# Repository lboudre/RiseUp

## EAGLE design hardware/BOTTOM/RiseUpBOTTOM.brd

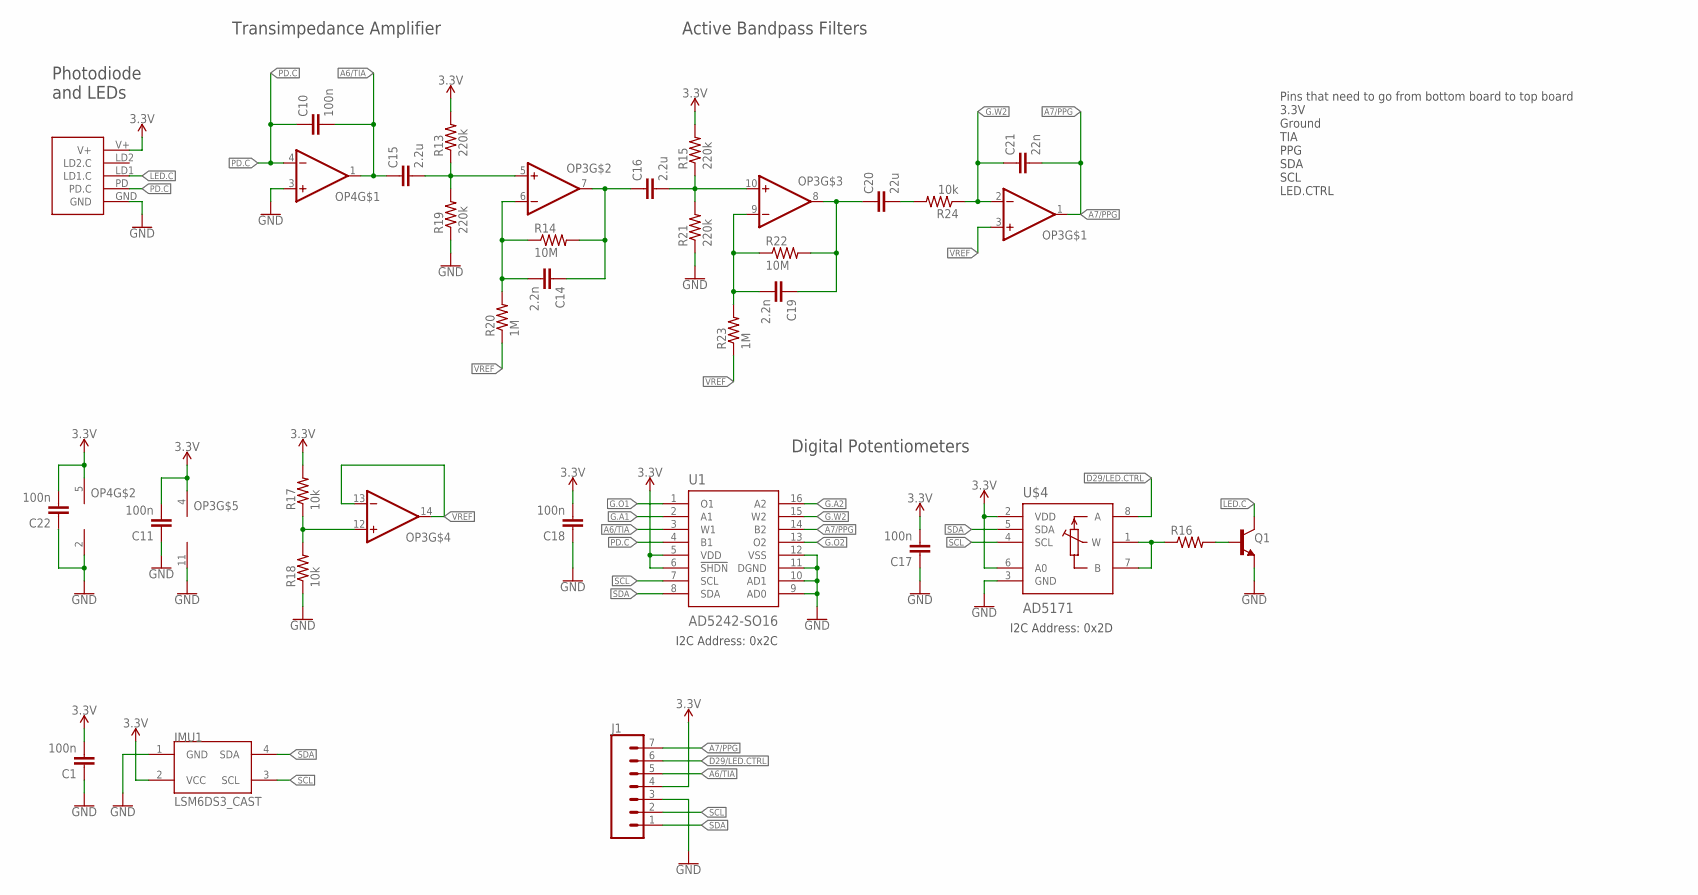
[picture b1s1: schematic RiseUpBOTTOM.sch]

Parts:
C1, C10, C11, C17, C18, C22: 100n; C0603
C14, C19: 2.2n; C0603
C15, C16: 2.2u; C0603
C20: 22u; C0603
C21: 22n; C0603
IMU1: LSM6DS3_CAST
J1: CONN_07; 1X07
OP3: OP-QUAD-SO14; SO14
OP4: OP-SINGLEOT; SOT23-5
Q1: NPN-GENERIC; SOT23-3
R13, R15, R19, R21: 220k; R0603
R14, R22: 10M; R0603
R16: RESISTOR0603; R0603
R17, R18: 10k; R0402
R20, R23: 1M; R0603
R24: 10k; R0603
U1: AD5242-SO16; SO16
U$3: PPG.MODULE.2
U$4: AD5171; SOT-23-8

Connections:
3.3V: C1.2, C11.2, C17.2, C18.2, C22.2, IMU1.2 (VCC), J1.4, OP3.4 (V+), OP4.5 (V+), R13.2, R15.2, R17.2, U1.5 (VDD), U1.6 (!SHDN), U$3.V+, U$4.2 (VDD), U$4.6 (A0)
A6/TIA: C10.2, C15.1, J1.5, OP4.1 (OUT), U1.3 (W1)
A7/PPG: C21.2, J1.7, OP3.1 (OUT), U1.14 (B2)
D29/LED.CTRL: J1.6, U$4.8 (A)
G.A1: U1.2 (A1)
G.A2: U1.16 (A2)
G.O1: U1.1 (O1)
G.O2: U1.13 (O2)
G.W2: C21.1, OP3.2 (-IN), R24.1, U1.15 (W2)
GND: C1.1, C11.1, C17.1, C18.1, C22.1, IMU1.1 (GND), J1.3, OP3.11 (V-), OP4.2 (V-), OP4.3 (+IN), Q1.2 (E), R18.1, R19.1, R21.1, U1.9 (AD0), U1.10 (AD1), U1.11 (DGND), U1.12 (VSS), U$3.GND, U$4.3 (GND)
LED.C: Q1.3 (C), U$3.LD1 (LD1.C)
unnamed: Q1.1 (B), R16.2
unnamed: R16.1, U$4.1 (W), U$4.7 (B)
unnamed: OP3.12 (+IN), R17.1, R18.2
unnamed: C15.2, OP3.5 (+IN), R13.1, R19.2
unnamed: C14.2, OP3.6 (-IN), R14.1, R20.2
unnamed: C14.1, C16.1, OP3.7 (OUT), R14.2
unnamed: C16.2, OP3.10 (+IN), R15.1, R21.2
unnamed: C19.2, OP3.9 (-IN), R22.1, R23.2
unnamed: C19.1, C20.1, OP3.8 (OUT), R22.2
unnamed: C20.2, R24.2
PD.C: C10.1, OP4.4 (-IN), U1.4 (B1), U$3.PD (PD.C)
SCL: IMU1.3 (SCL), J1.2, U1.7 (SCL), U$4.4 (SCL)
SDA: IMU1.4 (SDA), J1.1, U1.8 (SDA), U$4.5 (SDA)
VREF: OP3.3 (+IN), OP3.13 (-IN), OP3.14 (OUT), R20.1, R23.1

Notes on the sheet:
Photodiode and LEDs
Active Bandpass Filters
Digital Potentiometers
Transimpedance Amplifier
I2C Address: 0x2C
I2C Address: 0x2D
Pins that need to go from bottom board to top board 3.3V Ground TIA PPG SDA SCL LED.CTRL

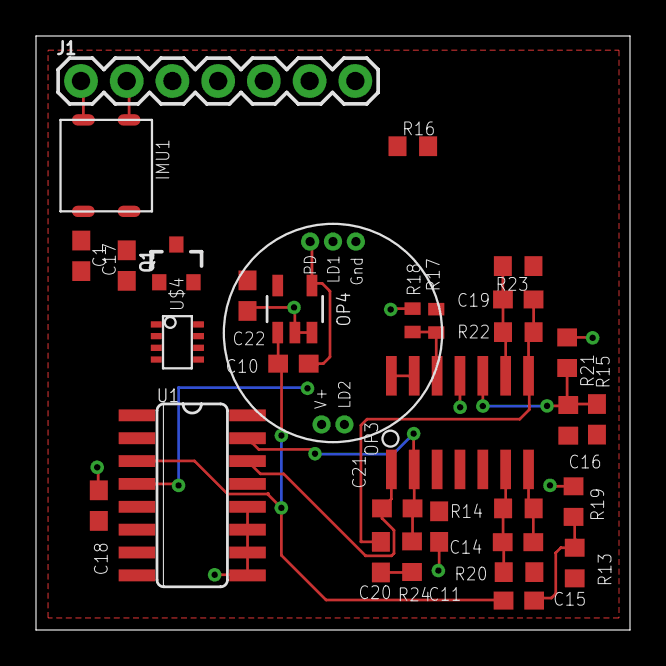
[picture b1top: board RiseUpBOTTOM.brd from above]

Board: 2 copper layers, 33.0 x 33.0 mm, 32 parts (0 on the bottom side), 21 nets.

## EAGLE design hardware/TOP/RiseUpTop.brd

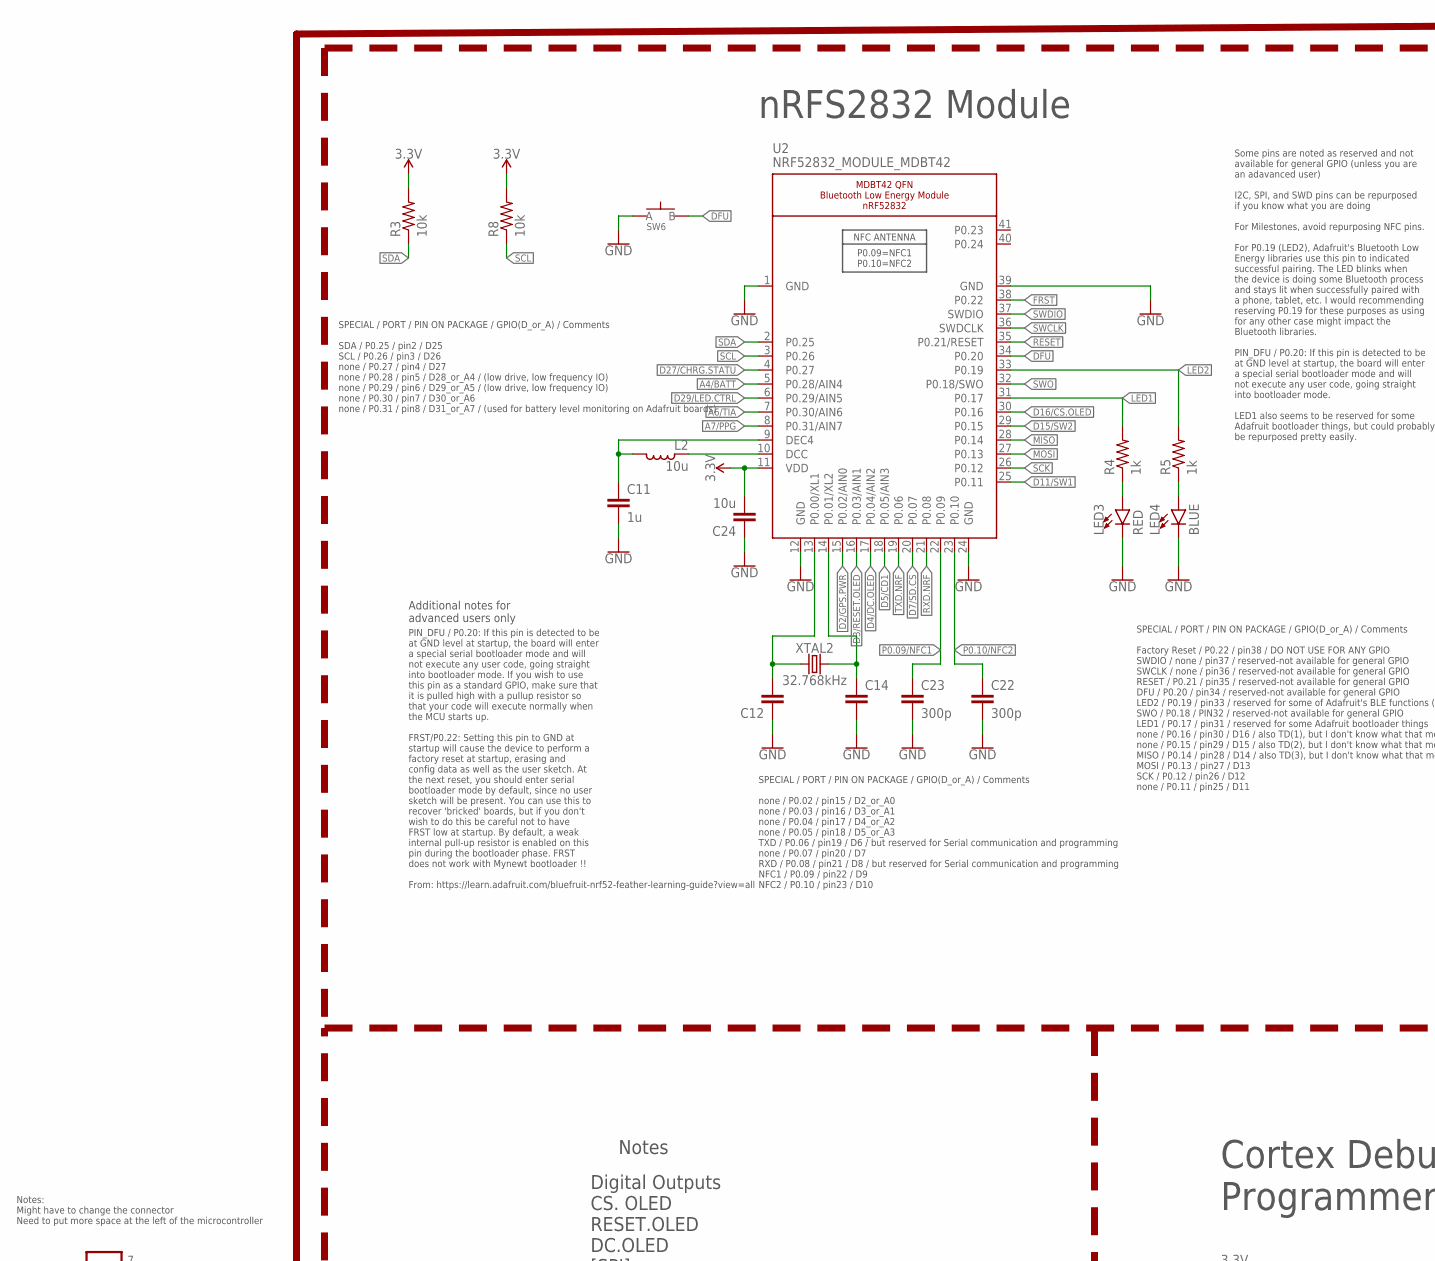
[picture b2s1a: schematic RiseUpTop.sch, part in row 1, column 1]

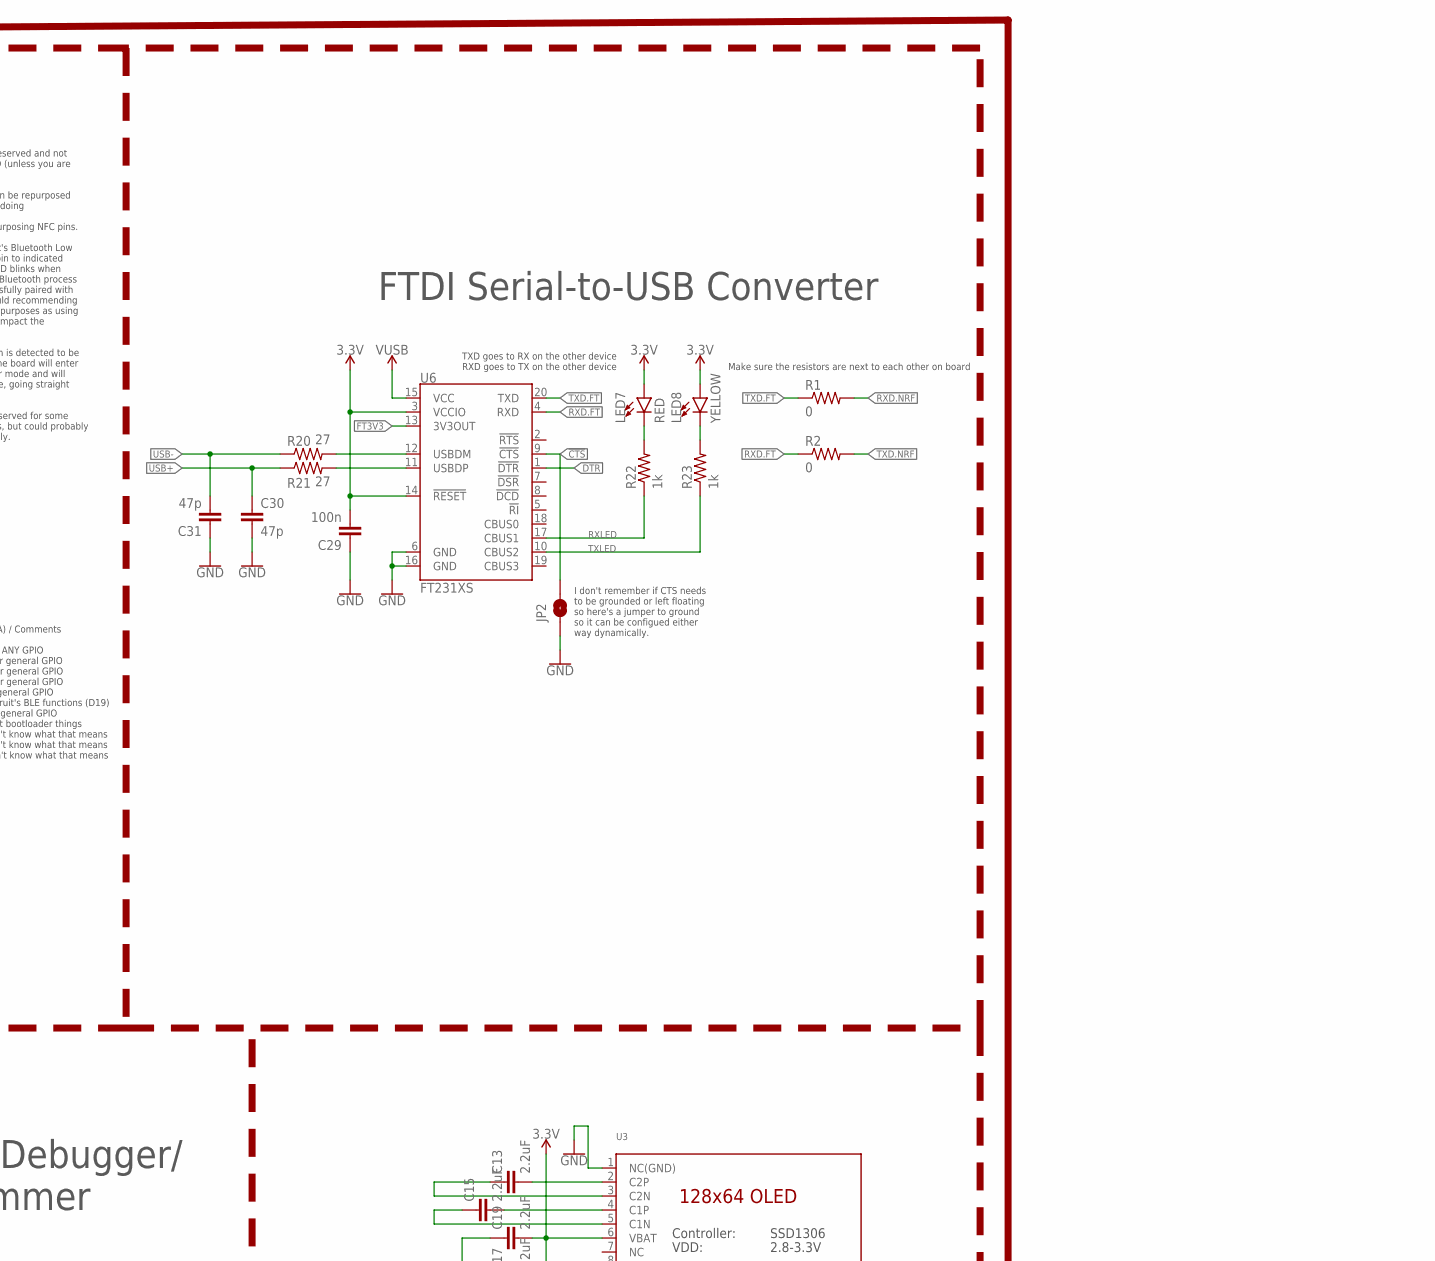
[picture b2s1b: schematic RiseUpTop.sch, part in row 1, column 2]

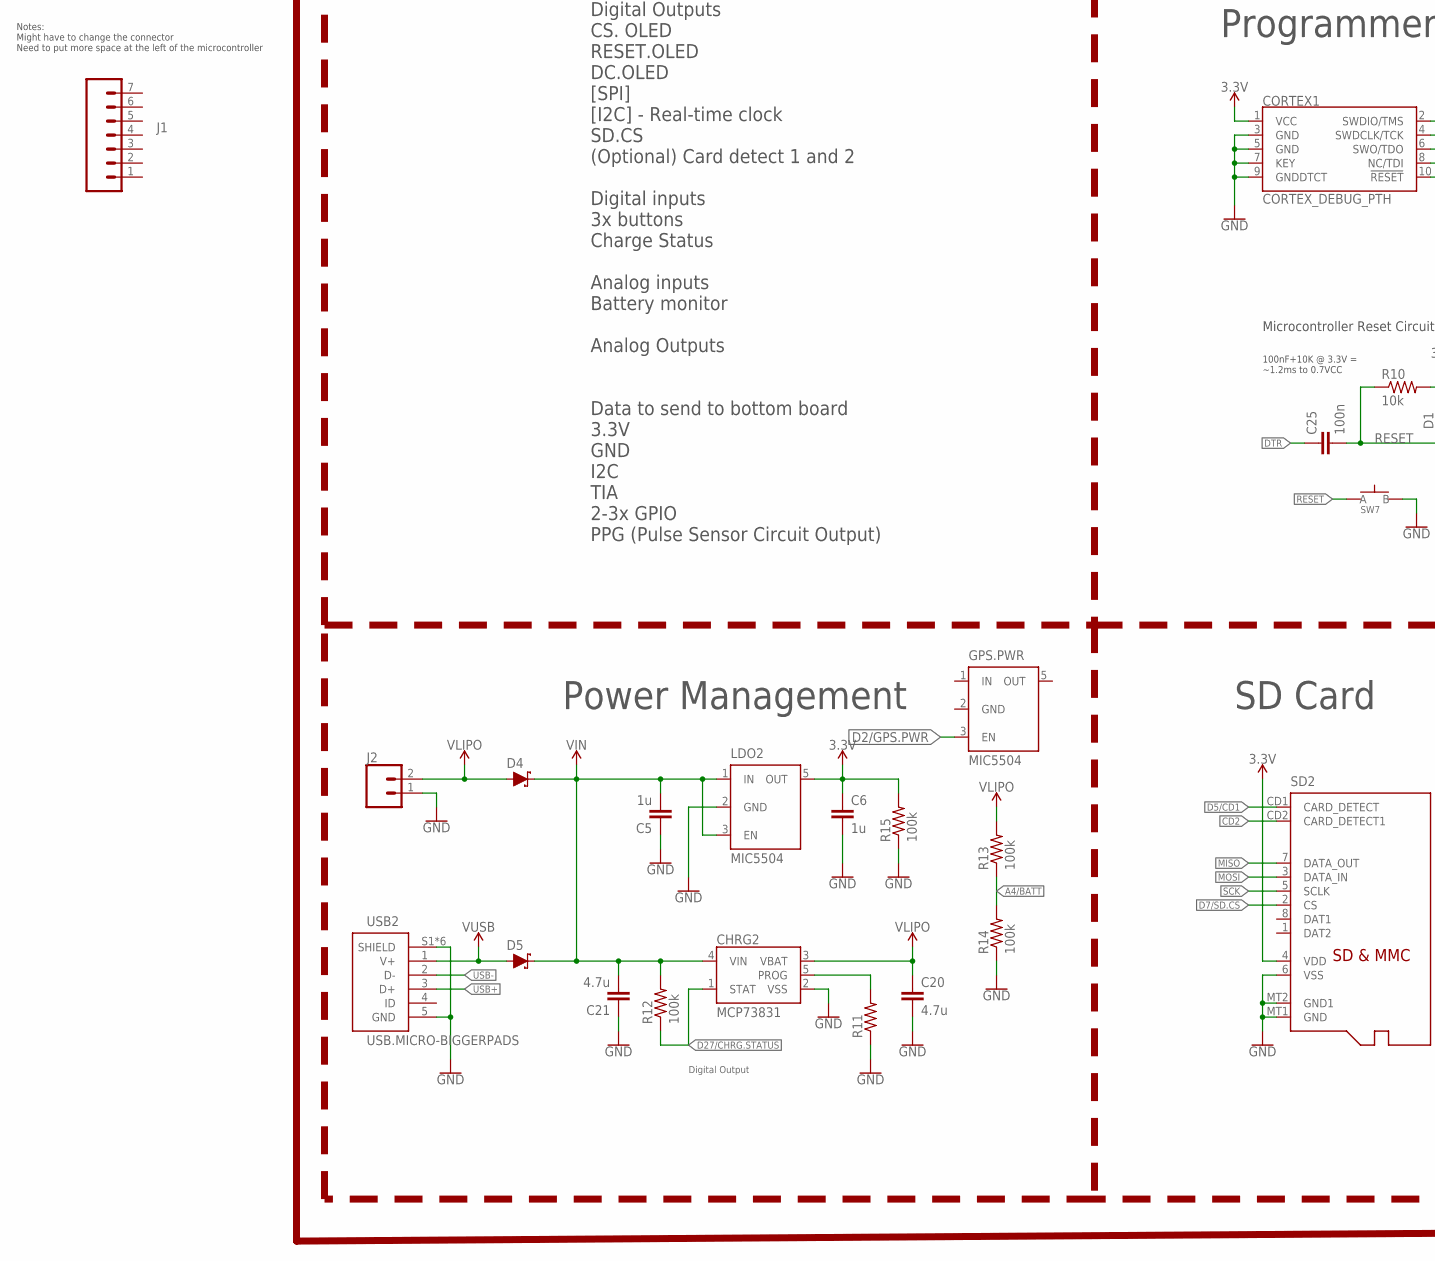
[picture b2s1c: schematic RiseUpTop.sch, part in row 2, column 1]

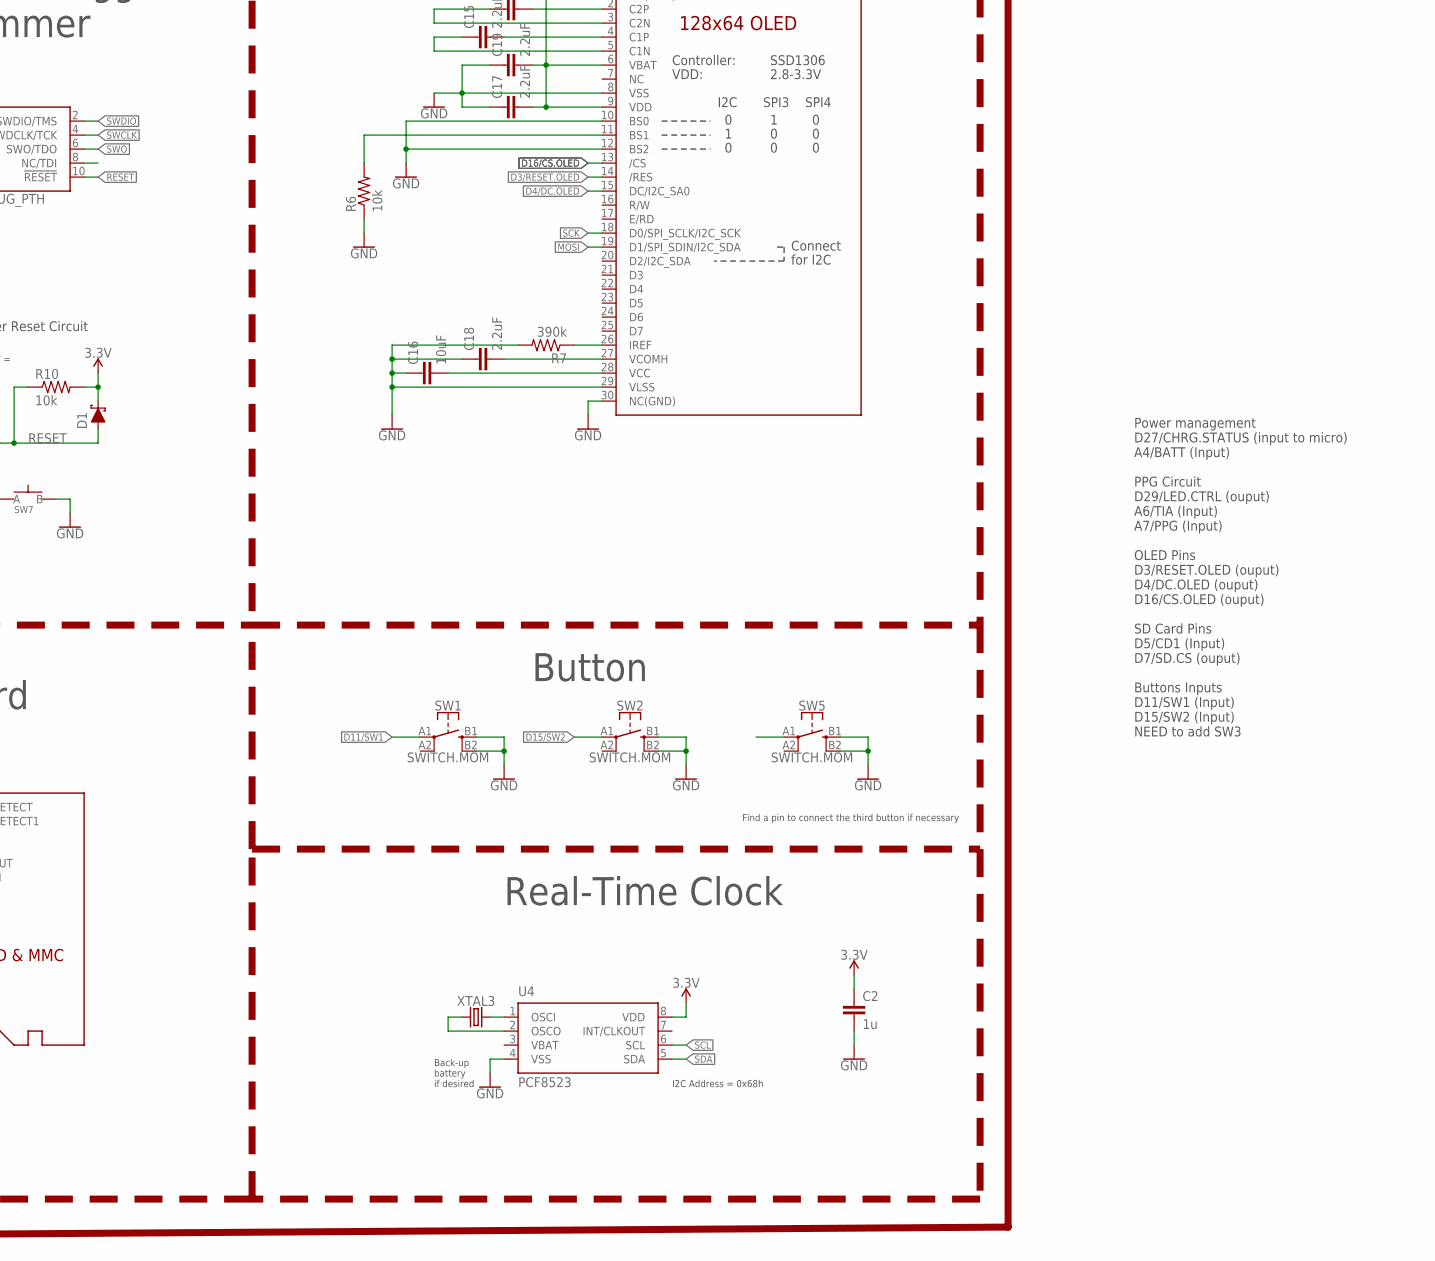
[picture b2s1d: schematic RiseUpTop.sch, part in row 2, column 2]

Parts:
C2, C5, C6, C11: 1u; C0603
C12, C14: CAPACITOR0603; C0603
C13, C15, C17, C18, C19: 2.2uF; C0402
C16: 10uF; C0603
C20, C21: 4.7u; C0603
C22, C23: 300p; C0603
C24: 10u; C0805
C25, C29: 100n; C0603
C30, C31: 47p; C0603
CHRG2: MCP73831; SOT23-5
CORTEX1: CORTEX_DEBUG_PTH; 2X5-PTH-1.27MM
D1, D4, D5: SCHOTTKY-USC; USC
GPS.PWR: MIC5504; SOT23-5
J1: CONN_07; 1X07
J2: CONN_02; 1X02
JP2: JUMPER-SMT_2_NO_SILK; SMT-JUMPER_2_NO_SILK
L2: 10u; L0603
LDO2: MIC5504; SOT23-5
LED3, LED7: RED; LED-0603
LED4: BLUE; LED-0603
LED8: YELLOW; LED-0603
R1, R2: 0; R0603
R3, R6, R8, R10: 10k; R0603
R4, R5, R22, R23: 1k; R0603
R7: 390k; R0603
R11: RESISTOR0603; R0603
R12, R13, R14, R15: 100k; R0603
R20, R21: 27; R0603
SD2: MICROSD
SW1, SW2, SW5: SWITCH.MOM; TACTILE_SWITCH_SMD_6.2MM_TALL
SW6, SW7: SPST-PTS830GG140-COPY.1-3; BUTTON-GULLWING
U2: NRF52832_MODULE_MDBT42; BLE_MODULE_RAYTAC_MDBT42
U3: DISP_OLED_UG-2864HSWEG01-NO-WRAPAROUND; UG-2864HSWEG01_0.96IN_NO-WRAPAROUND
U4: PCF8523; SO8; DIGIKEY 568-5306-1-ND
U6: FT231XS; SSOP20_L
USB2: USB.MICRO-BIGGERPADS; USB-MICRO-01.BIGGERPADS
XTAL2: 32.768kHz; 2-SMD.NOLEAD.2.0MMTO1.2MM
XTAL3: 32.7680kHz; 2-SMD.NOLEAD.2.0MMTO1.2MM

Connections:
3.3V: C2.1, C6.1, C17.2, C19.2, C24.2, C29.2, CORTEX1.1 (VCC), D1.- (C), LDO2.5 (OUT), LED7.A, LED8.A, R3.2, R8.2, R10.2, R15.2, SD2.4 (VDD), U2.11 (VDD), U3.6 (VBAT), U3.9 (VDD), U4.8 (VDD), U6.3 (VCCIO), U6.14 (!RESET)
!CTS: JP2.2, U6.9 (!CTS)
A4/BATT: R13.1, R14.2, U2.5 (P0.28/AIN4)
A6/TIA: U2.7 (P0.30/AIN6)
A7/PPG: U2.8 (P0.31/AIN7)
CD2: SD2.CD2 (CARD_DETECT1)
D2/GPS.PWR: GPS.PWR.3 (EN), U2.15 (P0.02/AIN0)
D3/RESET.OLED: U2.16 (P0.03/AIN1), U3.14 (/RES)
D4/DC.OLED: U2.17 (P0.04/AIN2), U3.15 (DC/I2C_SA0)
D5/CD1: SD2.CD1 (CARD_DETECT), U2.18 (P0.05/AIN3)
D7/SD.CS: SD2.2 (CS), U2.20 (P0.07)
D11/SW1: SW1.A1 (1), U2.25 (P0.11)
D15/SW2: SW2.A1 (1), U2.29 (P0.15)
D16/CS.OLED: U2.30 (P0.16), U3.13 (/CS)
D16/SW3: SW5.A1 (1)
D27/CHRG.STATU: U2.4 (P0.27)
D27/CHRG.STATUS: CHRG2.1 (STAT), R12.1
D29/LED.CTRL: U2.6 (P0.29/AIN5)
DFU: SW6.3 (B), U2.34 (P0.20)
DTR: C25.1, U6.1 (!DTR)
FRST: U2.38 (P0.22)
FT3V3: U6.13 (3V3OUT)
GND: C2.2, C5.1, C6.2, C11.2, C12.1, C14.2, C16.1, C17.1, C18.1, C19.1, C20.2, C21.1, C22.2, C23.2, C24.1, C29.1, C30.2, C31.1, CHRG2.2 (VSS), CORTEX1.3 (GND), CORTEX1.5 (GND), CORTEX1.7 (KEY), CORTEX1.9 (GNDDTCT), J2.1, JP2.1, LDO2.2 (GND), LED3.C, LED4.C, R6.1, R7.2, R11.1, R14.1, R15.1, SD2.6 (VSS), SD2.MT1 (GND), SD2.MT2 (GND1), SW1.B1 (3), SW1.B2 (4), SW2.B1 (3), SW2.B2 (4), SW5.B1 (3), SW5.B2 (4), SW6.1 (A), SW7.3 (B), U2.1 (GND), U2.12 (GND), U2.24 (GND), U2.39 (GND), U3.1 (NC(GND)), U3.8 (VSS), U3.10 (BS0), U3.12 (BS2), U3.29 (VLSS), U3.30 (NC(GND)), U4.4 (VSS), U6.6 (GND), U6.16 (GND), USB2.5 (GND), USB2.S1 (SHIELD), USB2.S2 (SHIELD), USB2.S3 (SHIELD), USB2.S4 (SHIELD), USB2.S5 (SHIELD), USB2.S6 (SHIELD)
LED1: R4.2, U2.31 (P0.17)
LED2: R5.2, U2.33 (P0.19)
MISO: SD2.7 (DATA_OUT), U2.28 (P0.14)
MOSI: SD2.3 (DATA_IN), U2.27 (P0.13), U3.19 (D1/SPI_SDIN/I2C_SDA)
unnamed: R6.2, U3.11 (BS1)
unnamed: R7.1, U3.26 (IREF)
unnamed: C13.2, U3.2 (C2P)
unnamed: U4.2 (OSCO), XTAL3.P$1 (1)
unnamed: C13.1, U3.3 (C2N)
unnamed: U4.1 (OSCI), XTAL3.P$2 (2)
unnamed: C15.2, U3.4 (C1P)
unnamed: C15.1, U3.5 (C1N)
unnamed: C16.2, U3.28 (VCC)
unnamed: C18.2, U3.27 (VCOMH)
unnamed: C12.2, U2.13 (P0.00/XL1), XTAL2.P$1 (1)
unnamed: CHRG2.5 (PROG), R11.2
unnamed: C14.1, U2.14 (P0.01/XL2), XTAL2.P$2 (2)
unnamed: LED3.A, R4.1
unnamed: LED4.A, R5.1
unnamed: L2.1, U2.10 (DCC)
unnamed: C11.1, L2.2, U2.9 (DEC4)
unnamed: R20.2, U6.12 (USBDM)
unnamed: R21.2, U6.11 (USBDP)
unnamed: LED7.C, R22.2
unnamed: LED8.C, R23.2
P0.09/NFC1: C23.1, U2.22 (P0.09)
P0.10/NFC2: C22.1, U2.23 (P0.10)
RESET: C25.2, CORTEX1.10 (!RESET), D1.+ (A), R10.1, SW7.1 (A), U2.35 (P0.21/RESET)
RXD.FT: R2.1, U6.4 (RXD)
RXD.NRF: R1.2, U2.21 (P0.08)
RXLED: R22.1, U6.17 (CBUS1)
SCK: SD2.5 (SCLK), U2.26 (P0.12), U3.18 (D0/SPI_SCLK/I2C_SCK)
SCL: R8.1, U2.3 (P0.26), U4.6 (SCL)
SDA: R3.1, U2.2 (P0.25), U4.5 (SDA)
SWCLK: CORTEX1.4 (SWDCLK/TCK), U2.36 (SWDCLK)
SWDIO: CORTEX1.2 (SWDIO/TMS), U2.37 (SWDIO)
SWO: CORTEX1.6 (SWO/TDO), U2.32 (P0.18/SWO)
TXD.FT: R1.1, U6.20 (TXD)
TXD.NRF: R2.2, U2.19 (P0.06)
TXLED: R23.1, U6.10 (CBUS2)
USB+: C30.1, R21.1, USB2.3 (D+)
USB-: C31.2, R20.1, USB2.2 (D-)
VBAT: U4.3 (VBAT)
VIN: C5.2, C21.2, CHRG2.4 (VIN), D4.- (C), D5.- (C), LDO2.1 (IN), LDO2.3 (EN), R12.2
VLIPO: C20.1, CHRG2.3 (VBAT), D4.+ (A), J2.2, R13.2
V_USB: D5.+ (A), U6.15 (VCC), USB2.1 (V+)

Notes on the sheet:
nRFS2832 Module
Power Management
SD Card
Button
Real-Time Clock
Cortex Debugger/ Programmer
Digital Outputs CS. OLED RESET.OLED DC.OLED [SPI] [I2C] - Real-time clock SD.CS (Optional) Card detect 1 and 2 Digital inputs 3x buttons Charge Status Analog inputs Battery monitor Analog Outputs Data to send to bottom board 3.3V GND I2C TIA 2-3x GPIO PPG (Pulse Sensor Circuit Output)
TXD goes to RX on the other device RXD goes to TX on the other device
I don't remember if CTS needs to be grounded or left floating so here's a jumper to ground so it can be configued either way dynamically.
Microcontroller Reset Circuit
100nF+10K @ 3.3V = ~1.2ms to 0.7VCC
SPECIAL / PORT / PIN ON PACKAGE / GPIO(D_or_A) / Comments SDA / P0.25 / pin2 / D25 SCL / P0.26 / pin3 / D26 none / P0.27 / pin4 / D27 none / P0.28 / pin5 / D28_or_A4 / (low drive, low frequency IO) none / P0.29 / pin6 / D29_or_A5 / (low drive, low frequency IO) none / P0.30 / pin7 / D30_or_A6 none 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
SPECIAL / PORT / PIN ON PACKAGE / GPIO(D_or_A) / Comments none / P0.02 / pin15 / D2_or_A0 none / P0.03 / pin16 / D3_or_A1 none / P0.04 / pin17 / D4_or_A2 none / P0.05 / pin18 / D5_or_A3 TXD / P0.06 / pin19 / D6 / but reserved for Serial communication and programming none / P0.07 / pin20 / D7 RXD / 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
SPECIAL / PORT / PIN ON PACKAGE / GPIO(D_or_A) / Comments Factory Reset / P0.22 / pin38 / DO NOT USE FOR ANY GPIO SWDIO / none / pin37 / reserved-not available for general GPIO SWCLK / none / pin36 / reserved-not available for general GPIO RESET / P0.21 / pin35 / reserved-not available for general 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
Some pins are noted as reserved and not available for general GPIO (unless you are an adavanced user) I2C, SPI, and SWD pins can be repurposed if you know what you are doing For Milestones, avoid repurposing NFC pins. For P0.19 (LED2), Adafruit's Bluetooth Low Energy libraries use this pin to indic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
PIN_DFU / P0.20: If this pin is detected to be at GND level at startup, the board will enter a special serial bootloader mode and will not execute any user code, going straight into bootloader mode. If you wish to use this pin as a standard GPIO, make sure that it is pulled high with a pullup resis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
Additional notes for advanced users only
I2C Address = 0x68h
Back-up battery if desired
FTDI Serial-to-USB Converter
Notes
Digital Output
Notes: Might have to change the connector Need to put more space at the left of the microcontroller
Make sure the resistors are next to each other on board
Find a pin to connect the third button if necessary
Power management D27/CHRG.STATUS (input to micro) A4/BATT (Input) PPG Circuit D29/LED.CTRL (ouput) A6/TIA (Input) A7/PPG (Input) OLED Pins D3/RESET.OLED (ouput) D4/DC.OLED (ouput) D16/CS.OLED (ouput) SD Card Pins D5/CD1 (Input) D7/SD.CS (ouput) Buttons Inputs D11/SW1 (Input) D15/SW2 (Input) NEED to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

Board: 2 copper layers, 67 parts (2 on the bottom side), 60 nets, no tracks yet.

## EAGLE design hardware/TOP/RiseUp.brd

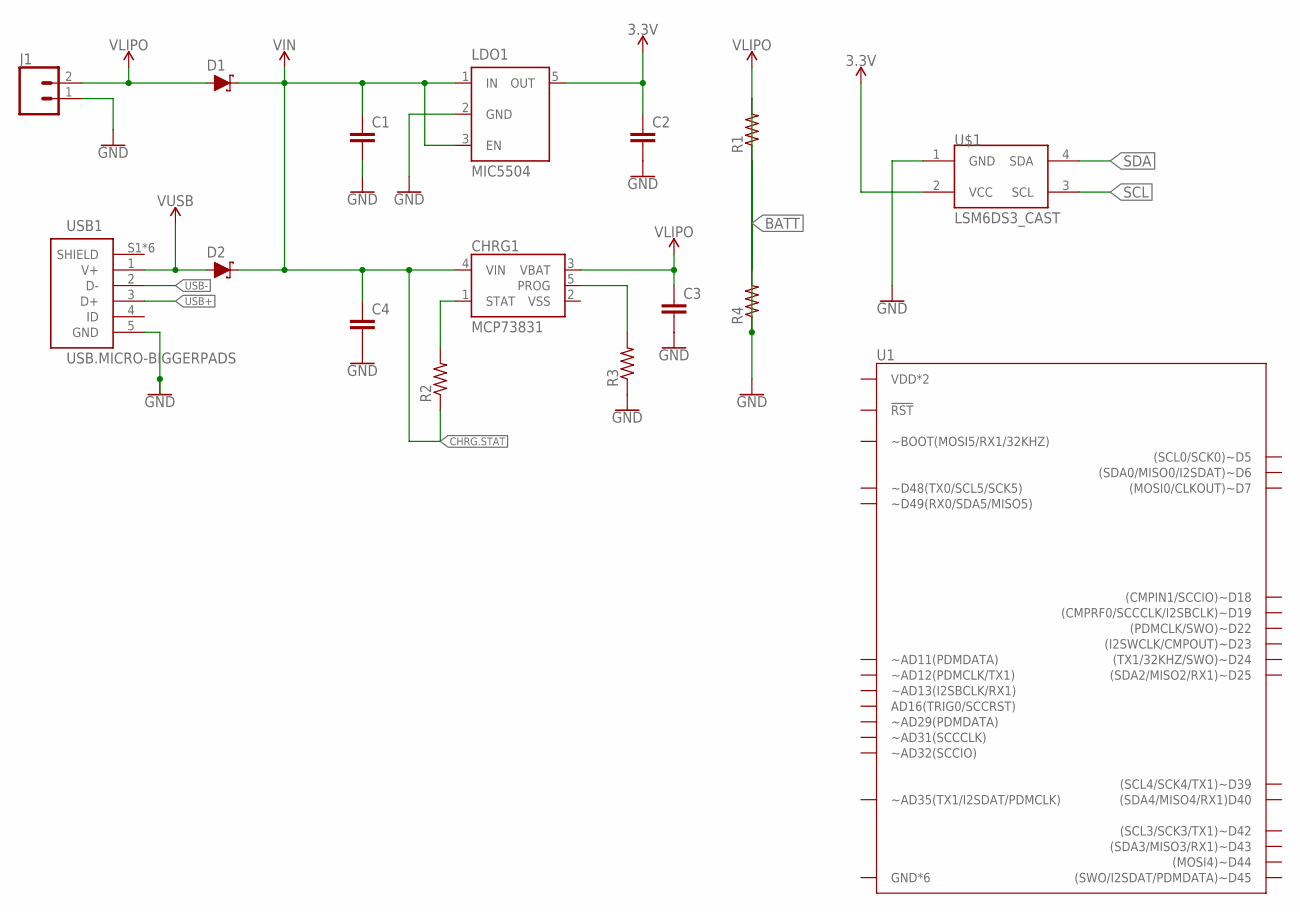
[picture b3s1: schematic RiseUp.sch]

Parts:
C1, C2, C3, C4: CAPACITOR0603; C0603
CHRG1: MCP73831; SOT23-5
D1, D2: SCHOTTKY-USC; USC
J1: CONN_02; 1X02
LDO1: MIC5504; SOT23-5
R1, R2, R3, R4: RESISTOR0603; R0603
U1: ARTEMIS.CAST; ARTEMIS_CAST
U$1: LSM6DS3_CAST
USB1: USB.MICRO-BIGGERPADS; USB-MICRO-01.BIGGERPADS

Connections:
3.3V: C2.1, LDO1.5 (OUT), U$1.2 (VCC)
BATT: R1.1, R4.2
CHRG.STAT: C1.1, C4.1, CHRG1.4 (VIN), D1.- (C), D2.- (C), LDO1.1 (IN), LDO1.3 (EN), R2.1
GND: C1.2, C2.2, C3.2, C4.2, J1.1, LDO1.2 (GND), R1.2, R3.1, R4.1, U$1.1 (GND), USB1.5 (GND)
unnamed: CHRG1.1 (STAT), R2.2
unnamed: CHRG1.5 (PROG), R3.2
SCL: U$1.3 (SCL)
SDA: U$1.4 (SDA)
USB+: USB1.3 (D+)
USB-: USB1.2 (D-)
VLIPO: C3.1, CHRG1.3 (VBAT), D1.+ (A), J1.2
VSS: CHRG1.2 (VSS)
V_USB: D2.+ (A), USB1.1 (V+)

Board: 2 copper layers, 16 parts (0 on the bottom side), 8 nets, no tracks yet.

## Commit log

2020-02-09 Added initial files
2020-05-28 feature list
2020-06-04 pushing from my mac and moving to windows
2020-06-04 reorganized firmware folders
2020-06-05 organizing hardware
2020-06-11 added RiseUpTop
2020-06-11 RiseUp schm
2020-06-11 updated TOP board
2020-06-11 start of Bottom board
2020-06-18 almost completed Top board
2020-06-18 Updated Bottom board from Take 2
2020-06-18 updated top from Take 2
2020-06-26 set up first arduino files
2020-07-02 Updates July2nd
2020-07-02 Updates end of July2nd, Start Take 03
2020-07-16 placing bottom board components
2020-07-17 Updated Bottom board Take 3
